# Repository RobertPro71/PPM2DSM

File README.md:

# PPM2DSM
Control with any transmitter a model with DSM receiver. All information about build, programming and use are here:
www.demoboard.de

## Folder Description

###Layout

The first modul. To build as a single modul that is temporarily connected to the transmitter.

### Layout_fix

A mod of the original converter. To use as fix connection to transmitter.

### Source

Sourcecode written in Arduino with all build tools.

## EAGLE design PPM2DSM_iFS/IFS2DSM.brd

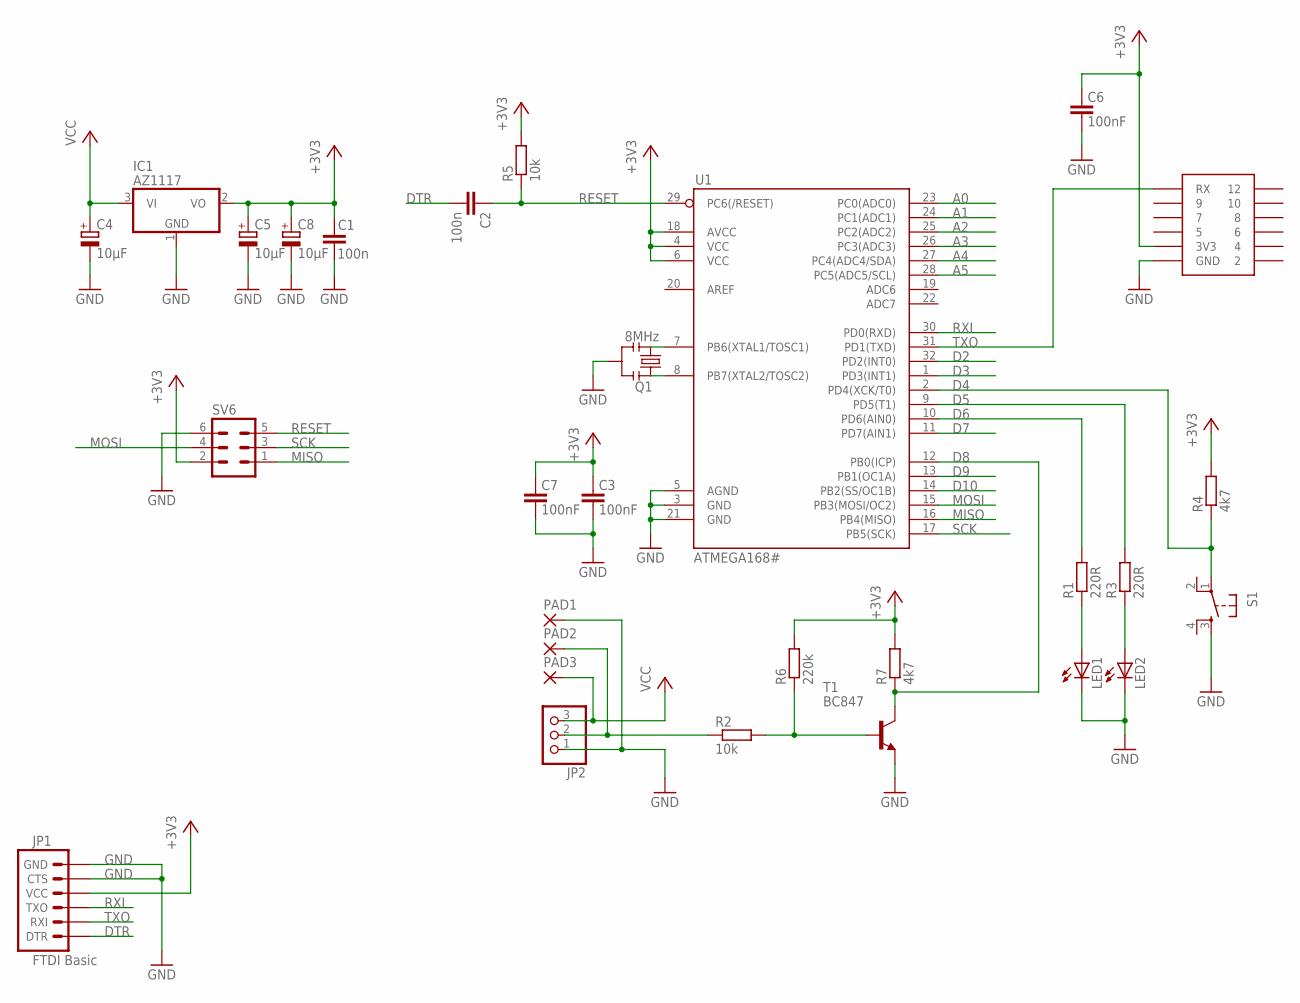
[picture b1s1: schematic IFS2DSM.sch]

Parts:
C1, C2: 100n; C0805
C3, C6, C7: 100nF; C0805
C4, C5, C8: 10µF; CT6032
IC1: AZ1117; SOT223
IC3: X1TX0
JP1: FTDI Basic; 1X06
JP2: PINHD-1X3_2.00; 1X03M
LED1, LED2: LEDSML0805; SML0805
PAD1, PAD2, PAD3: SMD2; SMD1,27-2,54
Q1: 8MHz; RESONATOR-SMD
R1, R3: 220R; R0805
R2, R5: 10k; R0805
R4, R7: 4k7; R0805
R6: 220k; R0805
S1: 10-XXTASTERSMD; SMD
SV6: MA03-2
T1: BC847; SOT23
U1: ATMEGA168#; TQFP32-08

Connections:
2: IC3.2
4: IC3.4
+3V3: C1.2, C3.2, C5.+, C6.2, C7.2, C8.+, IC1.2 (VO), IC3.3 (3V3), JP1.4 (VCC), R4.2, R5.2, R6.2, R7.2, SV6.2, U1.4 (VCC), U1.6 (VCC), U1.18 (AVCC)
A0: U1.23 (PC0(ADC0))
A1: U1.24 (PC1(ADC1))
A2: U1.25 (PC2(ADC2))
A3: U1.26 (PC3(ADC3))
A4: U1.27 (PC4(ADC4/SDA))
A5: U1.28 (PC5(ADC5/SCL))
D2: U1.32 (PD2(INT0))
D3: U1.1 (PD3(INT1))
D4: R4.1, S1.1, U1.2 (PD4(XCK/T0))
D5: R3.2, U1.9 (PD5(T1))
D6: R1.2, U1.10 (PD6(AIN0))
D7: U1.11 (PD7(AIN1))
D8: R7.1, T1.3 (C), U1.12 (PB0(ICP))
D9: U1.13 (PB1(OC1A))
D10: U1.14 (PB2(SS/OC1B))
DTR: C2.2, JP1.1 (DTR)
GND: C1.1, C3.1, C4.-, C5.-, C6.1, C7.1, C8.-, IC1.1 (GND), IC3.1 (GND), JP1.5 (CTS), JP1.6 (GND), JP2.1, LED1.C, LED2.C, PAD1.1, Q1.2, S1.3 (S), SV6.6, T1.2 (E), U1.3 (GND), U1.5 (AGND), U1.21 (GND)
MISO: SV6.1, U1.16 (PB4(MISO))
MOSI: SV6.4, U1.15 (PB3(MOSI/OC2))
unnamed: Q1.1, U1.8 (PB7(XTAL2/TOSC2))
unnamed: Q1.3, U1.7 (PB6(XTAL1/TOSC1))
unnamed: LED2.A, R3.1
unnamed: R2.2, R6.1, T1.1 (B)
unnamed: JP2.2, PAD2.1, R2.1
unnamed: LED1.A, R1.1
RESET: C2.1, R5.1, SV6.5, U1.29 (PC6(/RESET))
RXI: JP1.3 (TXO), U1.30 (PD0(RXD))
SCK: SV6.3, U1.17 (PB5(SCK))
TXO: IC3.11 (RX), JP1.2 (RXI), U1.31 (PD1(TXD))
VCC: C4.+, IC1.3 (VI), JP2.3, PAD3.1

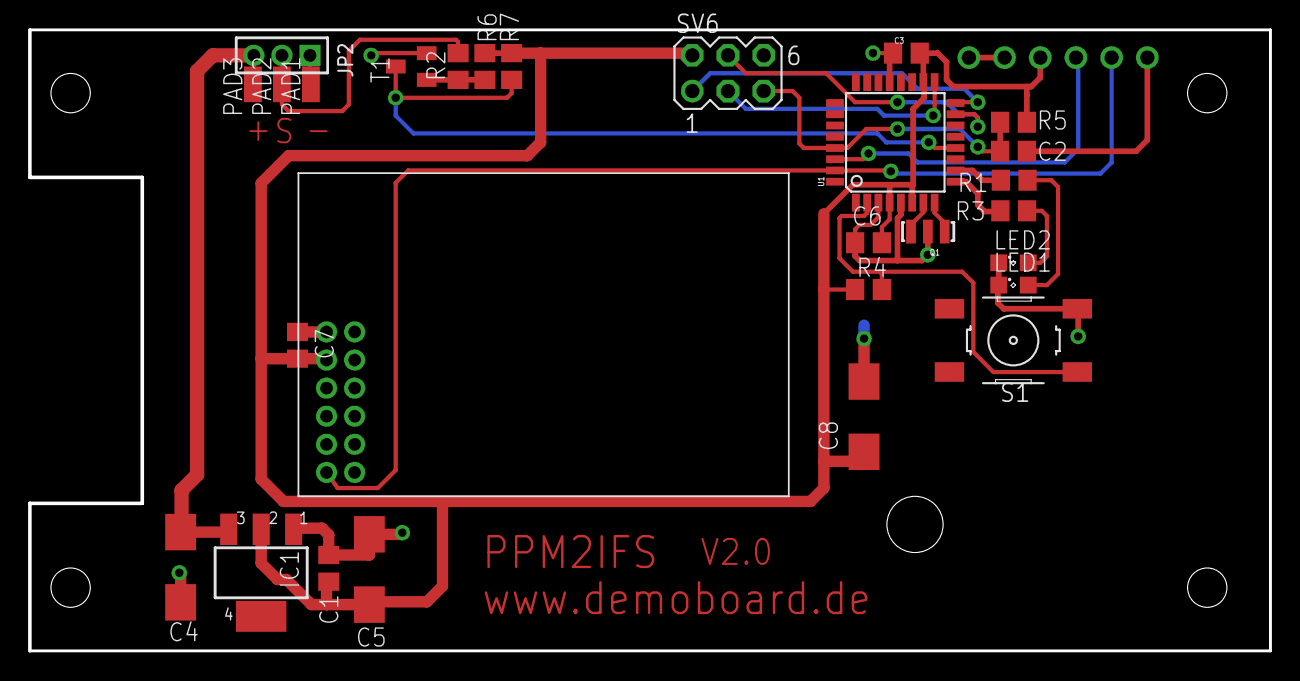
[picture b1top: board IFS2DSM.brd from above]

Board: 2 copper layers, 88.3 x 44.2 mm, 29 parts (1 on the bottom side), 20 nets.

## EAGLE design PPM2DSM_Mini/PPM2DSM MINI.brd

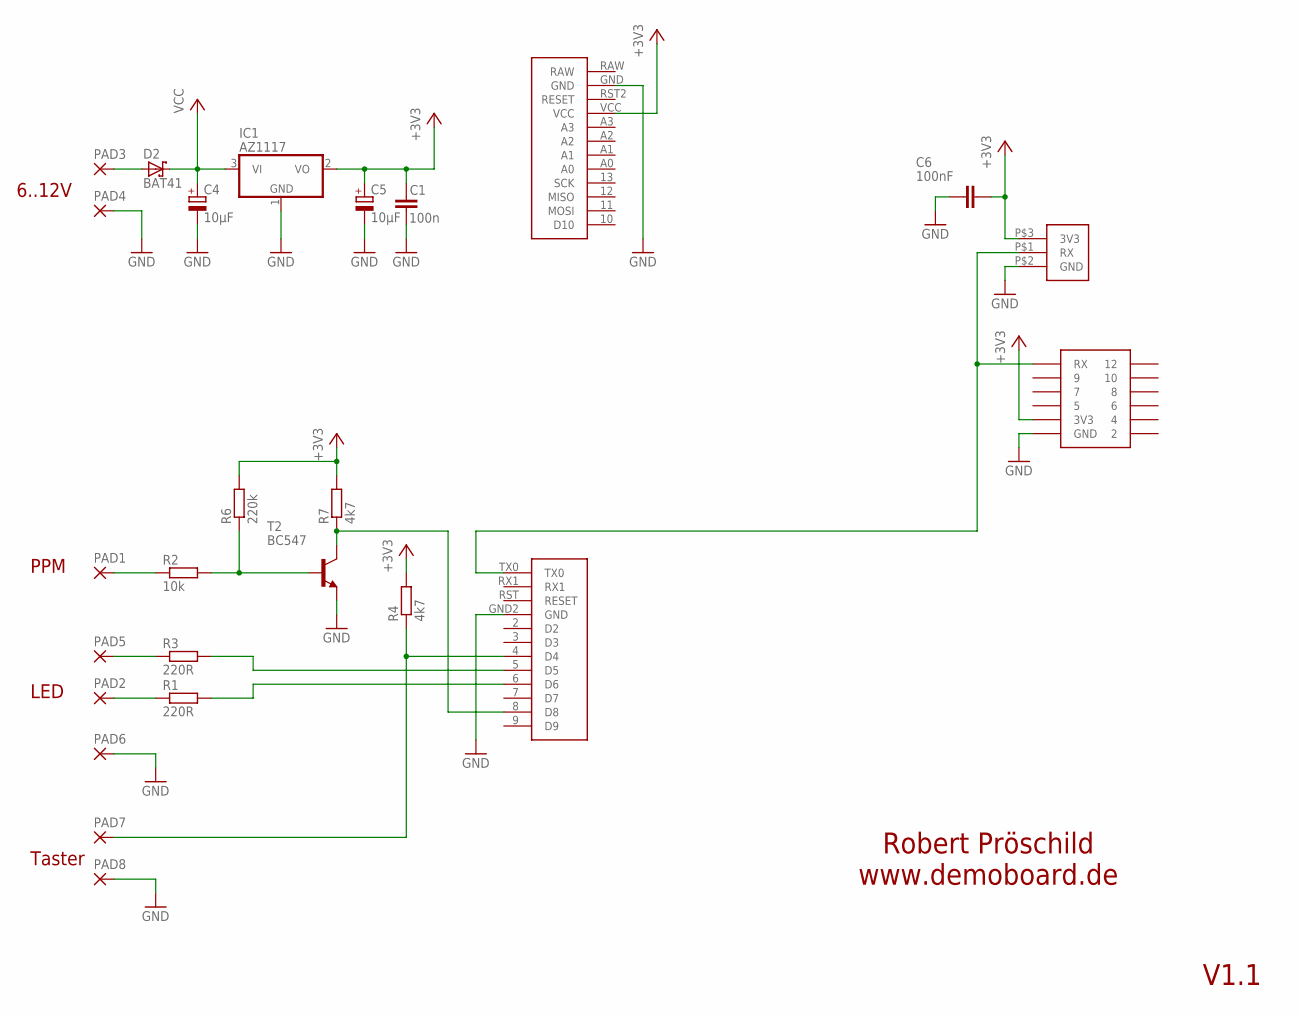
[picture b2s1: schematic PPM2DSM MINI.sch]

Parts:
C1: 100n; C025-024X044
C4, C5: 10µF; TT2D4
C6: 100nF; C025-024X044
D2: BAT41; DO35-7
IC1: AZ1117; SOT223
IC2: X10EMTX
IC3: MINI_PRO; PRO-MINI
IC4: X1TX0
PAD1, PAD2, PAD3, PAD4, PAD5, PAD6, PAD7, PAD8: SMD5; SMD2,54-5,08
R1, R3: 220R; 0204/5
R2: 10k; 0204/5
R4, R7: 4k7; 0204/5
R6: 220k; 0204/5
T2: BC547; TO92

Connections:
2: IC4.2
4: IC4.4
+3V3: C1.2, C5.+, C6.2, IC1.2 (VO), IC2.P$3 (3V3), IC3.VCC, IC4.3 (3V3), R4.2, R6.2, R7.2
A4: IC3.A4
A5: IC3.A5
D4: IC3.4 (D4), PAD7.1, R4.1
D5: IC3.5 (D5), R3.2
D6: IC3.6 (D6), R1.2
D8: IC3.8 (D8), R7.1, T2.3 (C)
GND: C1.1, C4.-, C5.-, C6.1, IC1.1 (GND), IC2.P$2 (GND), IC3.GND, IC3.GND2 (GND), IC4.1 (GND), PAD4.1, PAD6.1, PAD8.1, T2.1 (E)
unnamed: D2.A, PAD3.1
unnamed: R2.2, R6.1, T2.2 (B)
unnamed: PAD1.1, R2.1
unnamed: PAD2.1, R1.1
unnamed: PAD5.1, R3.1
RAW: IC3.RAW
TXO: IC2.P$1 (RX), IC3.TX0, IC4.11 (RX)
VCC: C4.+, D2.C, IC1.3 (VI)

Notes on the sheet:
6..12V
PPM
LED
Taster
Robert Pröschild www.demoboard.de
V1.1

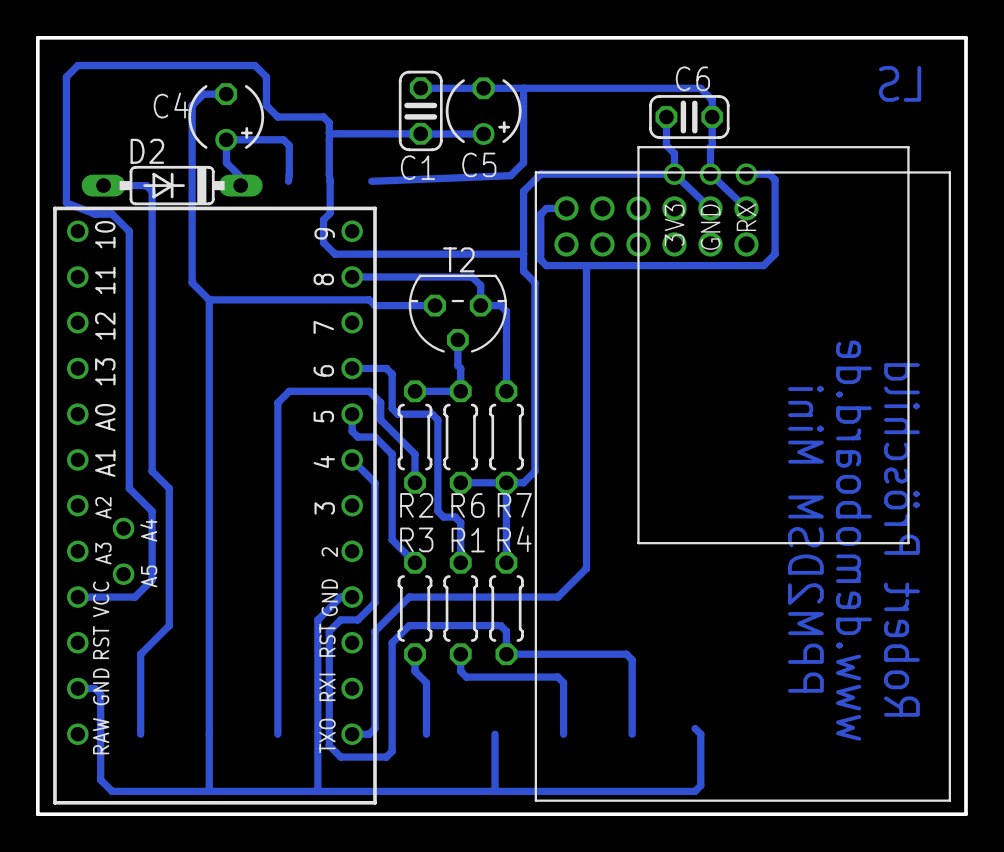
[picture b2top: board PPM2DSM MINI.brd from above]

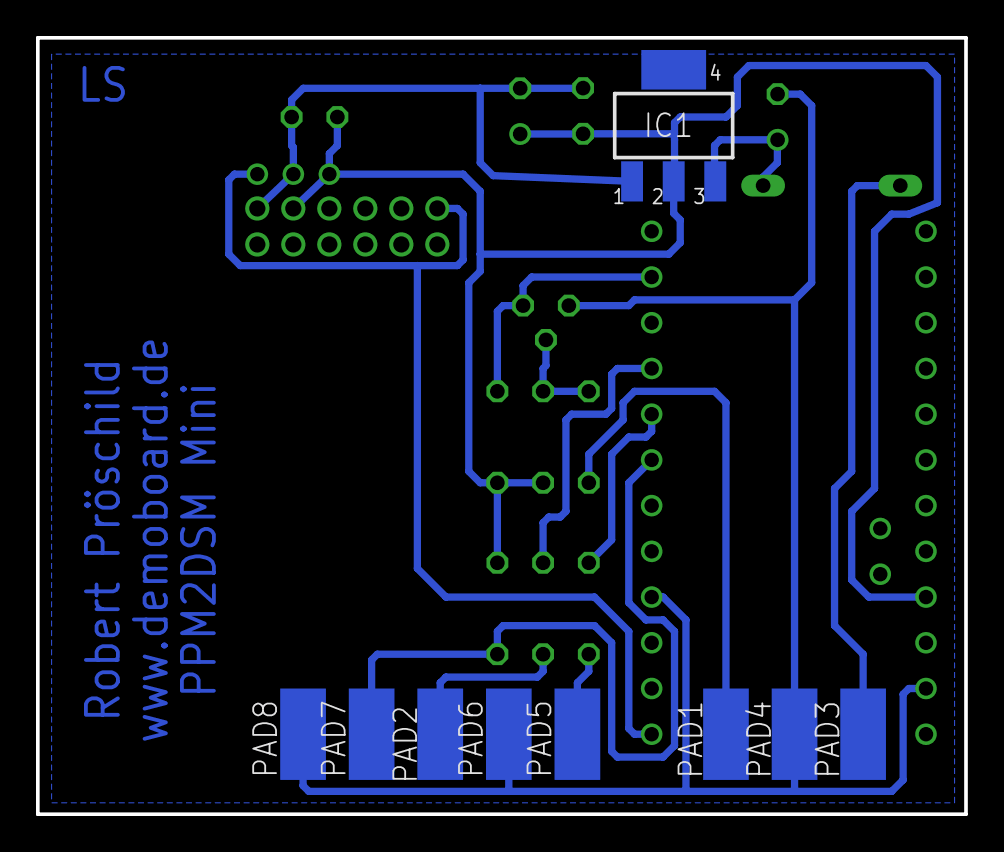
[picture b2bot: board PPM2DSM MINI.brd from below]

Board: 2 copper layers, 51.6 x 43.1 mm, 24 parts (9 on the bottom side), 13 nets.

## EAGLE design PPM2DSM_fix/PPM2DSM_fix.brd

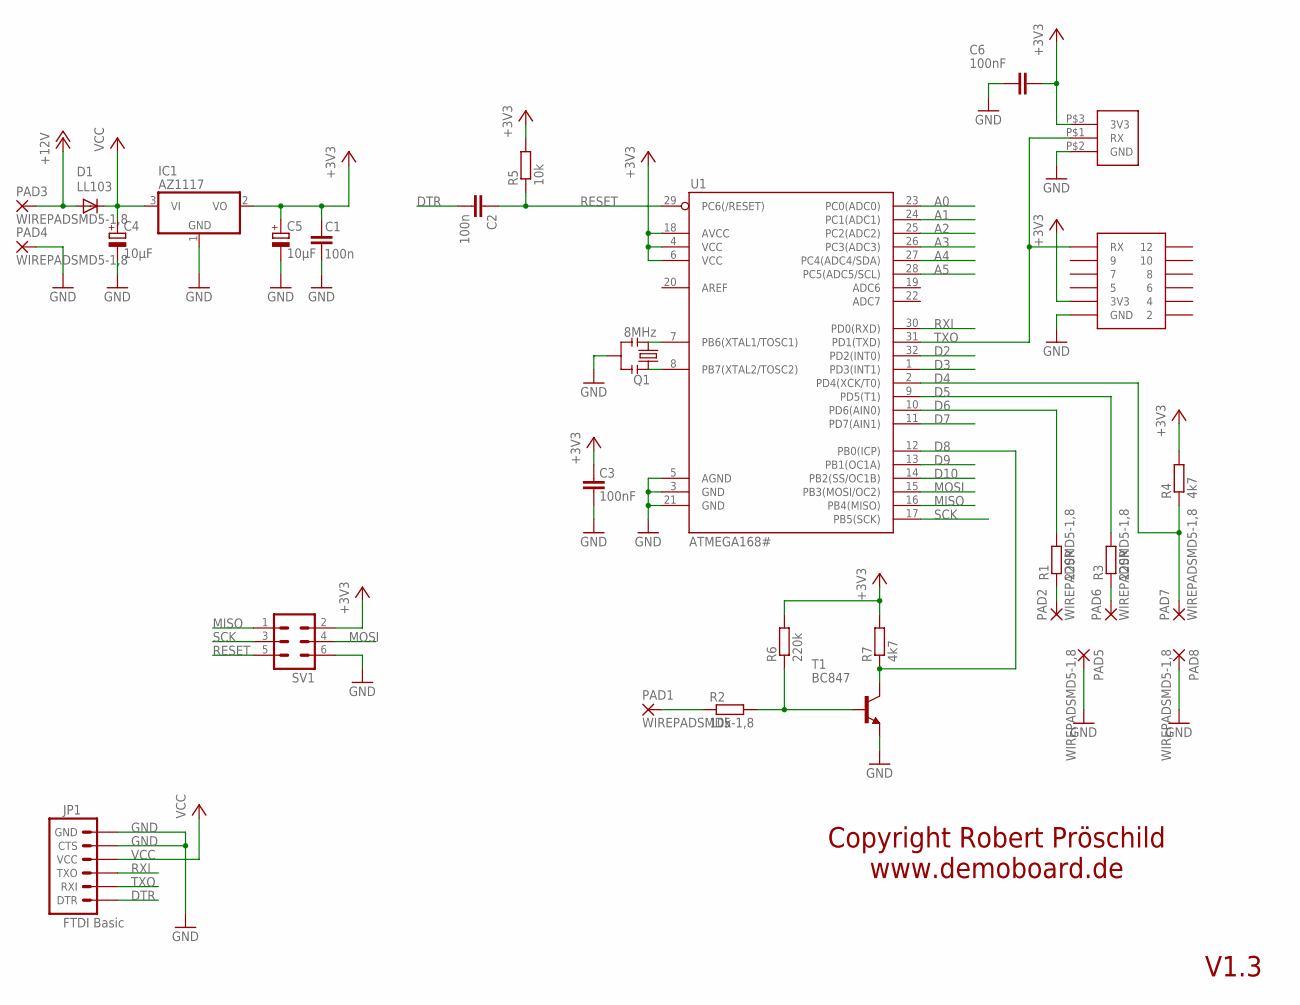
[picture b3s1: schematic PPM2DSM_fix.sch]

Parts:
C1, C2: 100n; C0805
C3, C6: 100nF; C0805
C4, C5: 10µF; CT6032
D1: LL103; MINIMELF
IC1: AZ1117; SOT223
IC2: X10EMTX
IC3: X1TX0
JP1: FTDI Basic; 1X06
PAD1, PAD2, PAD3, PAD4, PAD5, PAD6, PAD7, PAD8: WIREPADSMD5-1,8; 5-1,8
Q1: 8MHz; RESONATOR-SMD
R1, R3: 220R; R0805
R2, R5: 10k; R0805
R4, R7: 4k7; R0805
R6: 220k; R0805
SV1: MA03-2
T1: BC847; SOT23
U1: ATMEGA168#; TQFP32-08

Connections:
2: IC3.2
4: IC3.4
+3V3: C1.2, C3.2, C5.+, C6.2, IC1.2 (VO), IC2.P$3 (3V3), IC3.3 (3V3), R4.2, R5.2, R6.2, R7.2, SV1.2, U1.4 (VCC), U1.6 (VCC), U1.18 (AVCC)
+12V: D1.A, PAD3.1
A0: U1.23 (PC0(ADC0))
A1: U1.24 (PC1(ADC1))
A2: U1.25 (PC2(ADC2))
A3: U1.26 (PC3(ADC3))
A4: U1.27 (PC4(ADC4/SDA))
A5: U1.28 (PC5(ADC5/SCL))
D2: U1.32 (PD2(INT0))
D3: U1.1 (PD3(INT1))
D4: PAD7.1, R4.1, U1.2 (PD4(XCK/T0))
D5: R3.2, U1.9 (PD5(T1))
D6: R1.2, U1.10 (PD6(AIN0))
D7: U1.11 (PD7(AIN1))
D8: R7.1, T1.3 (C), U1.12 (PB0(ICP))
D9: U1.13 (PB1(OC1A))
D10: U1.14 (PB2(SS/OC1B))
DTR: C2.2, JP1.1 (DTR)
GND: C1.1, C3.1, C4.-, C5.-, C6.1, IC1.1 (GND), IC2.P$2 (GND), IC3.1 (GND), JP1.5 (CTS), JP1.6 (GND), PAD4.1, PAD5.1, PAD8.1, Q1.2, SV1.6, T1.2 (E), U1.3 (GND), U1.5 (AGND), U1.21 (GND)
MISO: SV1.1, U1.16 (PB4(MISO))
MOSI: SV1.4, U1.15 (PB3(MOSI/OC2))
unnamed: Q1.1, U1.8 (PB7(XTAL2/TOSC2))
unnamed: Q1.3, U1.7 (PB6(XTAL1/TOSC1))
unnamed: R2.2, R6.1, T1.1 (B)
unnamed: PAD1.1, R2.1
unnamed: PAD2.1, R1.1
unnamed: PAD6.1, R3.1
RESET: C2.1, R5.1, SV1.5, U1.29 (PC6(/RESET))
RXI: JP1.3 (TXO), U1.30 (PD0(RXD))
SCK: SV1.3, U1.17 (PB5(SCK))
TXO: IC2.P$1 (RX), IC3.11 (RX), JP1.2 (RXI), U1.31 (PD1(TXD))
VCC: C4.+, D1.C, IC1.3 (VI), JP1.4 (VCC)

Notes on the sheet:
Copyright Robert Pröschild www.demoboard.de
V1.3

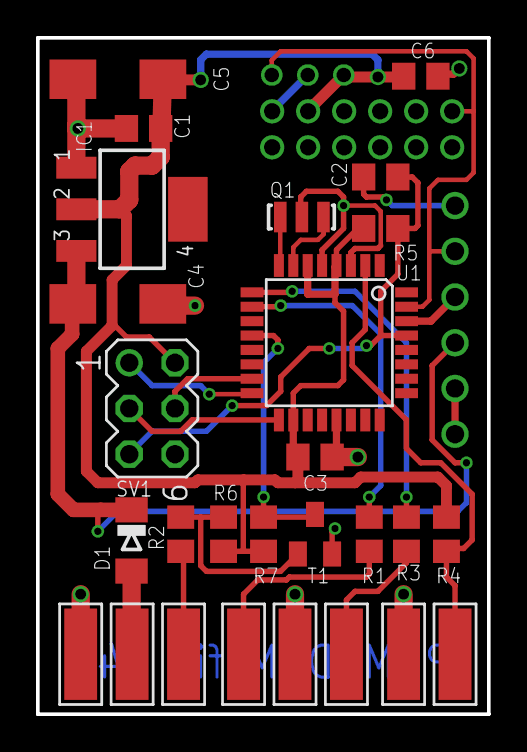
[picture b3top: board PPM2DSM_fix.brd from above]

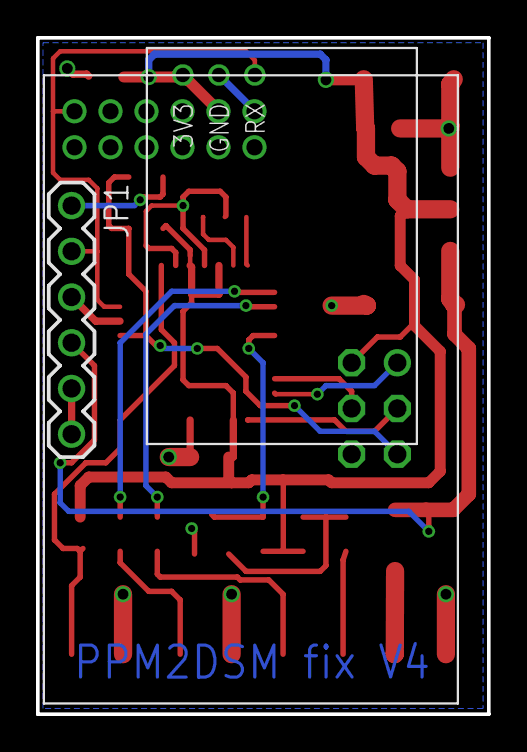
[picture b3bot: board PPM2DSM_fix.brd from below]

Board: 2 copper layers, 25.1 x 37.6 mm, 30 parts (3 on the bottom side), 21 nets.

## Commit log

2017-01-05 First Try
2017-04-11 Add PPM2DSM PCB
2017-04-11 Add PPM2DSM_fix PCB
2017-04-11 Add PPM2DSM MINI PCB
2017-04-11 Add Gerber files to use with elecrow
2017-04-11 Update gitignore
2017-04-11 Fly away, I like you source code. Find new friends and sometimes come back to this repo.
2018-04-22 Add iFS pcb

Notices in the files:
PPM2DSM_Mini/PPM2DSM MINI.brd:
Copyright by
Robert Pröschild
